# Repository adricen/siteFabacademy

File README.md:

adrien.centonze's website --> [See it online](http://fab.academany.org/2018/labs/fablabdigiscope/students/adrien-centonze/index.html)

# Multiple purpose machin

## Links:
* 3D files
( introduce a link from gitlab )

* Stocks Materials
  * 2 Delrin : 28€ / 500 mm² --> 12mm height
  * 1 DHCP : 26€ / 500 mm² --> 10mm height

* Electronics

###  Parametric 3D Model :
* [Process](#process)
  * [Inspiration](#inspi)
  * [Design Process](#design)
  * [Think about the stock](#stock)
  * [3D prototyping](#proto)
  * [Parametric design](#parametric)
* [Montage](#montage)
  * animated montage + video

###  Milling On the Shopbot OSB :
* [Preparation](#prepa)
  * [Create stock from reality](#stockCrea)
  * [Place elements](#places)
* [Setup](#setup)
  * [Stock](#stock)
  * [Orientation](#orientation)
  * [Zero point](#zero)
* [Tools](#tools)
  * [fablab speed and feeds calculators](#speedFeed)
  * [Setup your tools](#setTools)
* [Toolpaths](#toolpath)
  * [Parrallel 3D](#parrallele)
  * [Milling](#mill)
  * [2D Pocket](#pocket)
  * [2D contour](#contour)

### Machin Design

---

###  Design thinking :
####  Process
##### **Inspiration :**

To begin with this machin we choose to take two machin as reference. The first one is the one from Hector and the second one came from Nadya.   

#####  **Designing :**
The main goal we wanted to succed in making this machin so that anybody who have access to a milling machin could do this.

##### **Think about the stock and your machin :**
There is two main constrain that you couldn't avoid when doing a machin like that it's your stack, what size and weight is it.

##### milling prototyping
In order to know more about rack and minion, I made a first rack and minino with a junk of wood we had here in the lab.

Then I wanted to be sure of the joinery I made, so I made a simple milling test on our shopbot.

##### 3D prototyping
To be sure about the join I used I made some rapid prototyping with the milling machin first, and then with the 3D printer.

##### Parametric design
I know that I would have to make a lot of back and forth to succed to make this machin so I worked on making the joinery parametricaly depending on my stock height and my the smaller mill I have that could go that deep.

##### Montage
  ( animated montage + video )

###  Milling :
#### Preparation
##### Create stock from reality

Start by making a virtual reproducion of your stock. The Pom / Delerain we have make 500mmx501mm

##### Place elements
##### Setup
##### Stock
##### Orientation
##### Zero point
##### Tools
##### fablab speed and feeds calculators
##### Setup your tools
##### Toolpaths
##### Parrallel 3D
##### Milling
##### 2D Pocket
##### 2D contour

#### Mounting
* [Making the holes for ( les visses )](#holes)

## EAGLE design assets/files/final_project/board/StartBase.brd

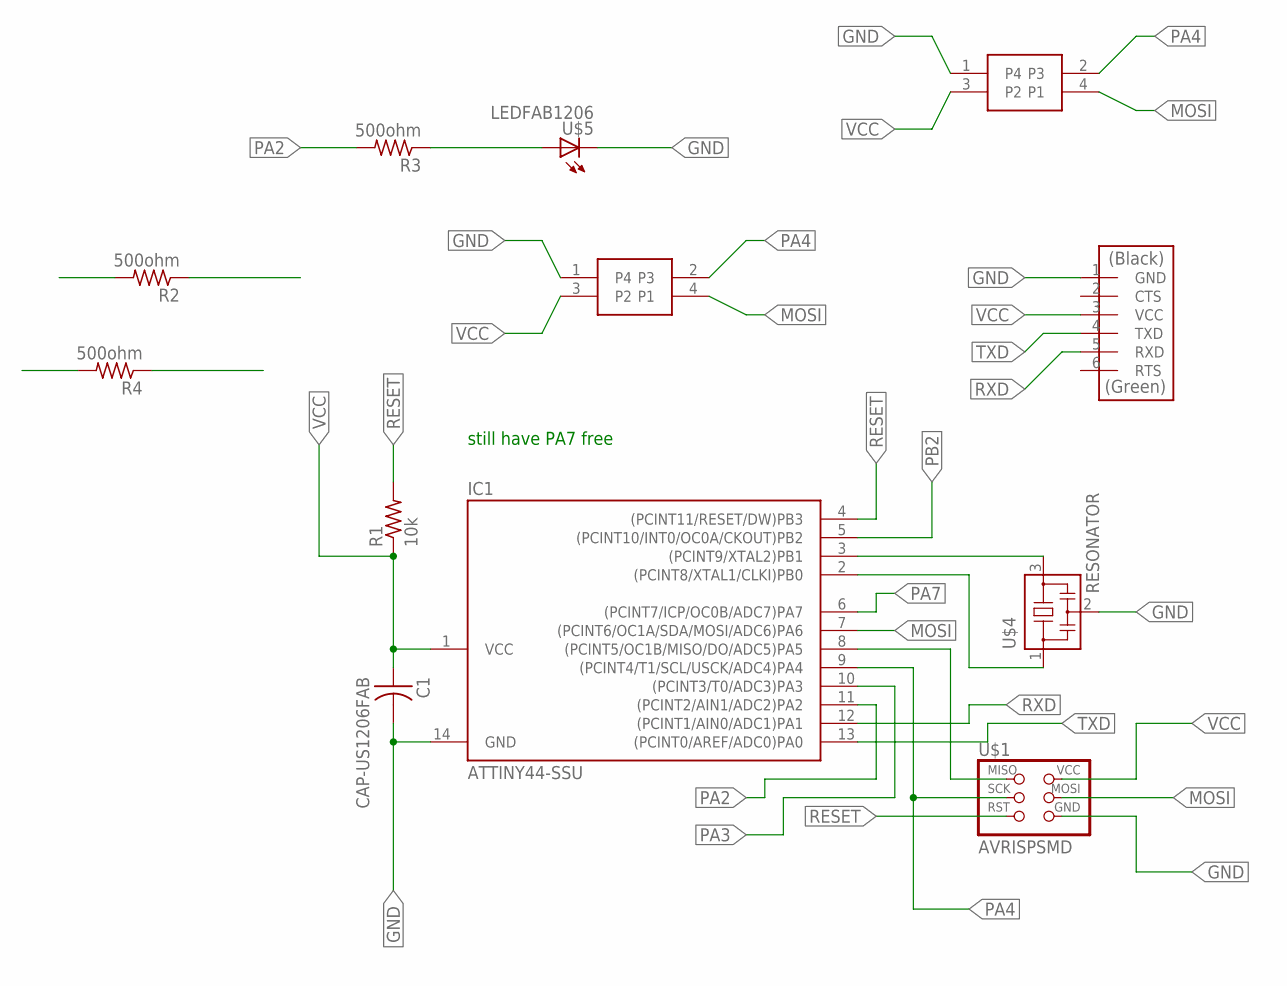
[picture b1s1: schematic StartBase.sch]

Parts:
C1: CAP-US1206FAB; C1206FAB
IC1: ATTINY44-SSU; SOIC14
R1: 10k; R1206FAB
R2, R3, R4: 500ohm; R1206FAB
U$1: AVRISPSMD; 2X03SMD
U$2: FTDI-SMD-HEADER; 1X06SMD
U$3, U$6: 4PIN-SMD-CONNECTOR; 2X02SMD
U$4: RESONATOR; EFOBM
U$5: LEDFAB1206; LED1206FAB

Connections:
GND: C1.2, IC1.14 (GND), U$1.6 (GND), U$2.1 (GND), U$3.1 (P4), U$4.2, U$5.2 (C), U$6.1 (P4)
MOSI: IC1.7 ((PCINT6/OC1A/SDA/MOSI/ADC6)PA6), U$1.4 (MOSI), U$3.4 (P1), U$6.4 (P1)
unnamed: IC1.3 ((PCINT9/XTAL2)PB1), U$4.3
unnamed: IC1.2 ((PCINT8/XTAL1/CLKI)PB0), U$4.1
unnamed: IC1.8 ((PCINT5/OC1B/MISO/DO/ADC5)PA5), U$1.1 (MISO)
unnamed: R3.1, U$5.1 (A)
PA1: R2.2
PA2: IC1.11 ((PCINT2/AIN1/ADC2)PA2), R3.2
PA3: IC1.10 ((PCINT3/T0/ADC3)PA3)
PA4: IC1.9 ((PCINT4/T1/SCL/USCK/ADC4)PA4), U$1.3 (SCK), U$3.2 (P3), U$6.2 (P3)
PA5: R4.2
PA7: IC1.6 ((PCINT7/ICP/OC0B/ADC7)PA7)
PB2: IC1.5 ((PCINT10/INT0/OC0A/CKOUT)PB2)
RESET: IC1.4 ((PCINT11/RESET/DW)PB3), R1.2, U$1.5 (RST)
RXD: IC1.12 ((PCINT1/AIN0/ADC1)PA1), U$2.5 (RXD)
TXD: IC1.13 ((PCINT0/AREF/ADC0)PA0), U$2.4 (TXD)
VCC: C1.1, IC1.1 (VCC), R1.1, U$1.2 (VCC), U$2.3 (VCC), U$3.3 (P2), U$6.3 (P2)

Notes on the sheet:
still have PA7 free

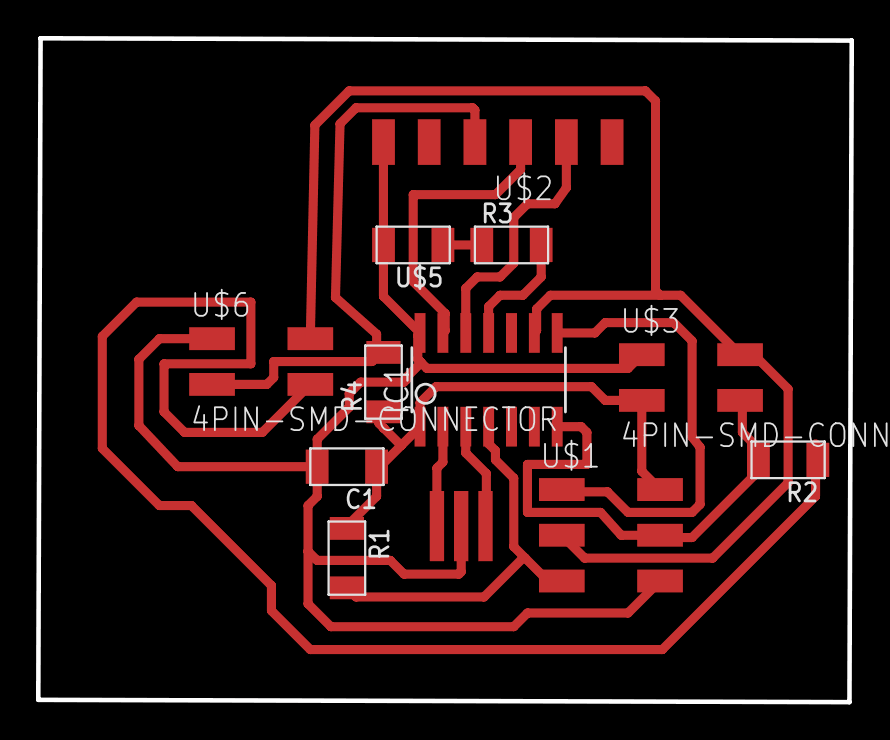
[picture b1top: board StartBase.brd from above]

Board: 2 copper layers, 45.2 x 36.9 mm, 12 parts (0 on the bottom side), 12 nets.

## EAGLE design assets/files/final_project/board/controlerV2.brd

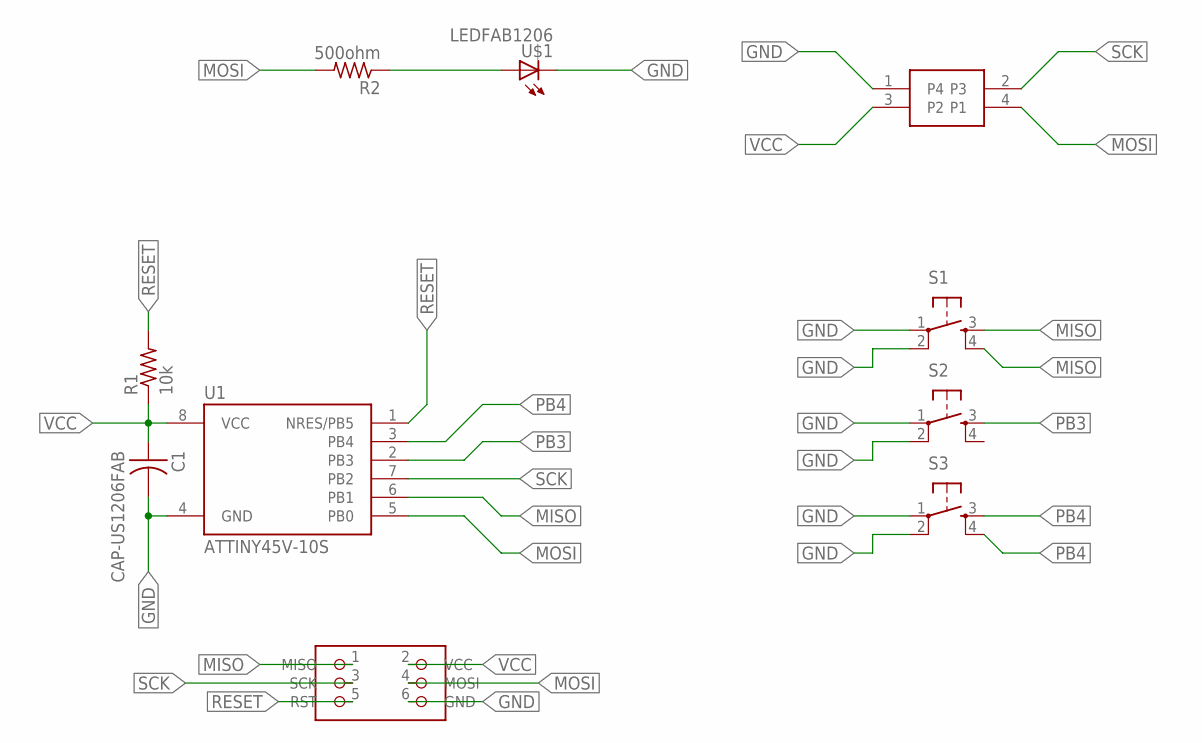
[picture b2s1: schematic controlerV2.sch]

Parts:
C1: CAP-US1206FAB; C1206FAB
R1: 10k; R1206
R2: 500ohm; R1206FAB
S1, S2, S3: 6MM_SWITCH6MM_SWITCH; 6MM_SWITCH
U1: ATTINY45V-10S; SOIC8_EIAJ_208MIL
U$1: LEDFAB1206; LED1206FAB
U$2: 4PIN-SMD-CONNECTOR; 2X02SMD
U$4: AVRISPSMD; 2X03SMD

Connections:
GND: C1.2, S1.1, S1.2 (P1), S2.1, S2.2 (P1), S3.1, S3.2 (P1), U1.4 (GND), U$1.2 (C), U$2.1 (P4), U$4.6 (GND)
MISO: S1.3 (S), S1.4 (S1), U1.6 (PB1), U$4.1 (MISO)
MOSI: R2.2, U1.5 (PB0), U$2.4 (P1), U$4.4 (MOSI)
unnamed: R2.1, U$1.1 (A)
PB3: S2.3 (S), U1.2 (PB3)
PB4: S3.3 (S), S3.4 (S1), U1.3 (PB4)
RESET: R1.2, U1.1 (NRES/PB5), U$4.5 (RST)
SCK: U1.7 (PB2), U$2.2 (P3), U$4.3 (SCK)
VCC: C1.1, R1.1, U1.8 (VCC), U$2.3 (P2), U$4.2 (VCC)

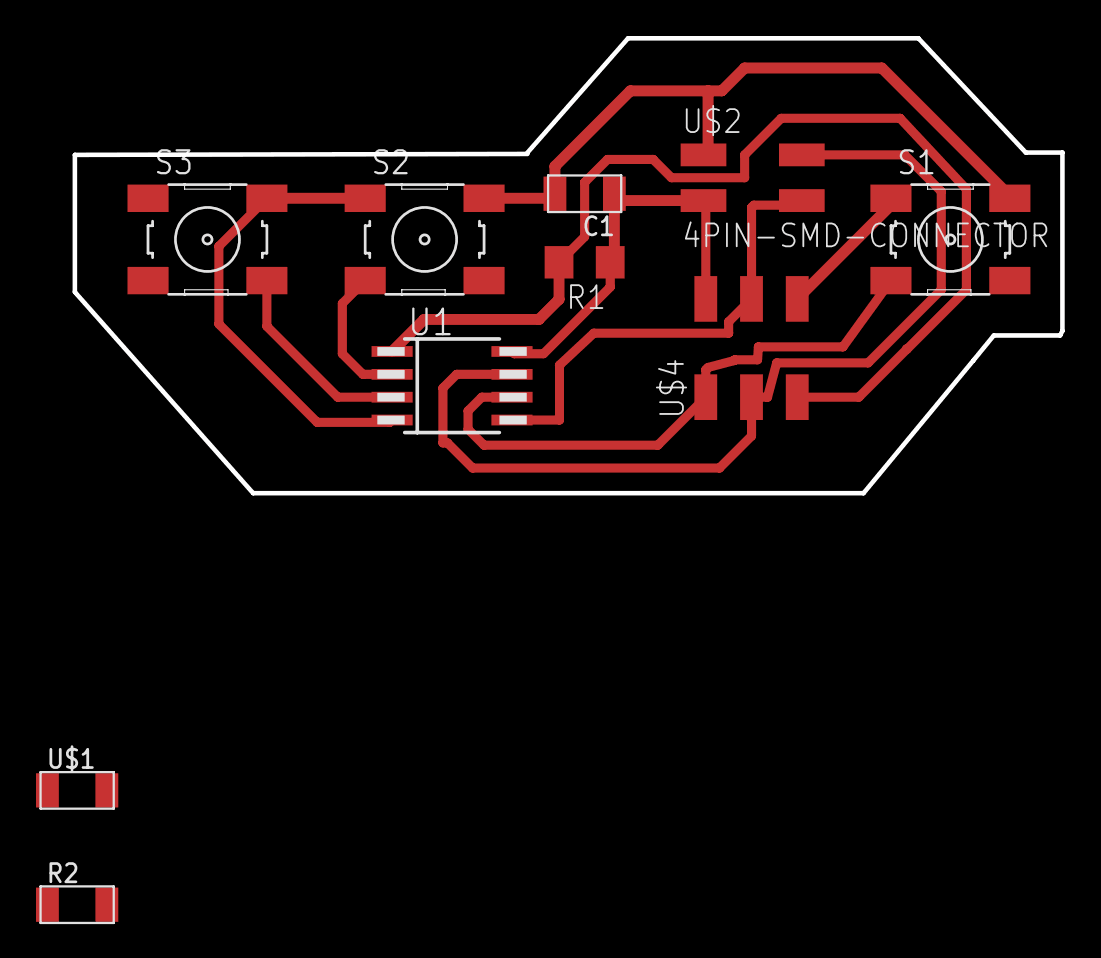
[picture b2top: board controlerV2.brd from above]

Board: 2 copper layers, 54.9 x 25.3 mm, 10 parts (0 on the bottom side), 9 nets.

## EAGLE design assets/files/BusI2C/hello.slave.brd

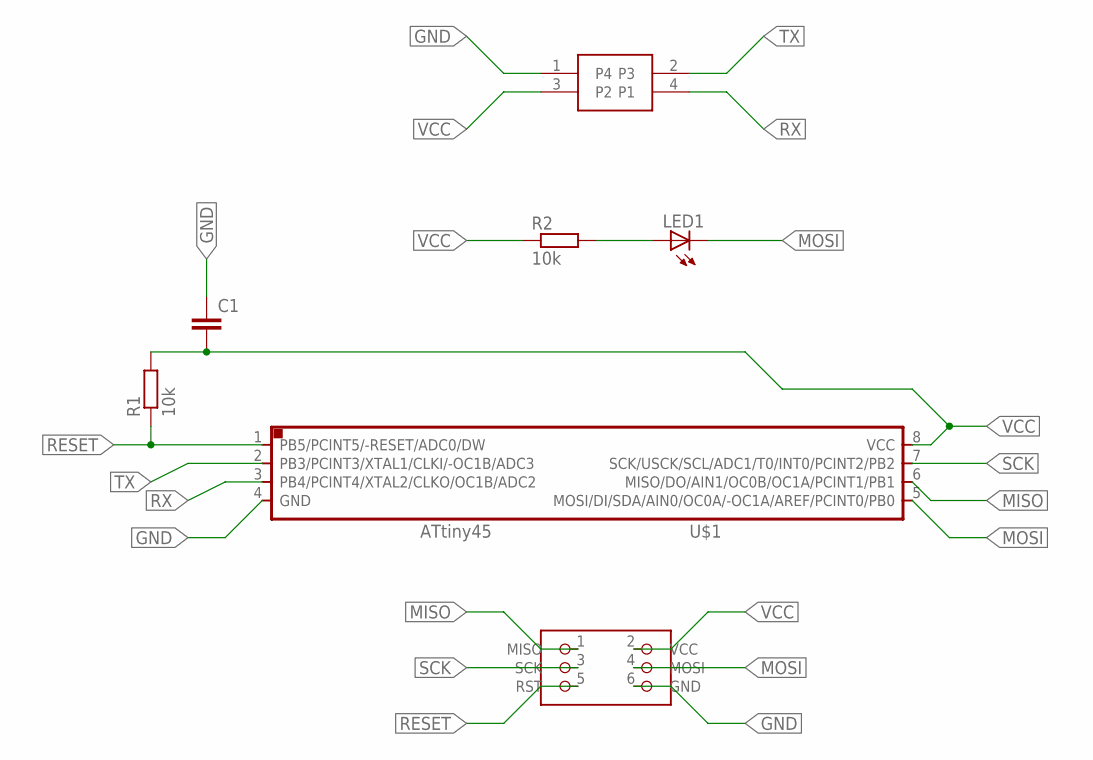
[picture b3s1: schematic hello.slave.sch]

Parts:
C1: C; C0805
LED1: LED_E; LED_1206
R1, R2: 10k; R0805
U$1: ATTINY45SI; SOIC8
U$2: AVRISPSMD; 2X03SMD
U$4: 4PIN-SMD-CONNECTOR; 2X02SMD

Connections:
GND: C1.1, U$1.4 (GND), U$2.6 (GND), U$4.1 (P4)
MISO: U$1.6 (MISO/DO/AIN1/OC0B/OC1A/PCINT1/PB1), U$2.1 (MISO)
MOSI: LED1.C, U$1.5 (MOSI/DI/SDA/AIN0/OC0A/-OC1A/AREF/PCINT0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), U$2.4 (MOSI)
unnamed: LED1.A, R2.2
RESET: R1.1, U$1.1 (PB5/PCINT5/-RESET/ADC0/DW), U$2.5 (RST)
RX: U$1.3 (PB4/PCINT4/XTAL2/CLKO/OC1B/ADC2), U$4.4 (P1)
SCK: U$1.7 (SCK/USCK/SCL/ADC1/T0/INT0/PCINT2/PB2), U$2.3 (SCK)
TX: U$1.2 (PB3/PCINT3/XTAL1/CLKI/-OC1B/ADC3), U$4.2 (P3)
VCC: C1.2, R1.2, R2.1, U$1.8 (VCC), U$2.2 (VCC), U$4.3 (P2)

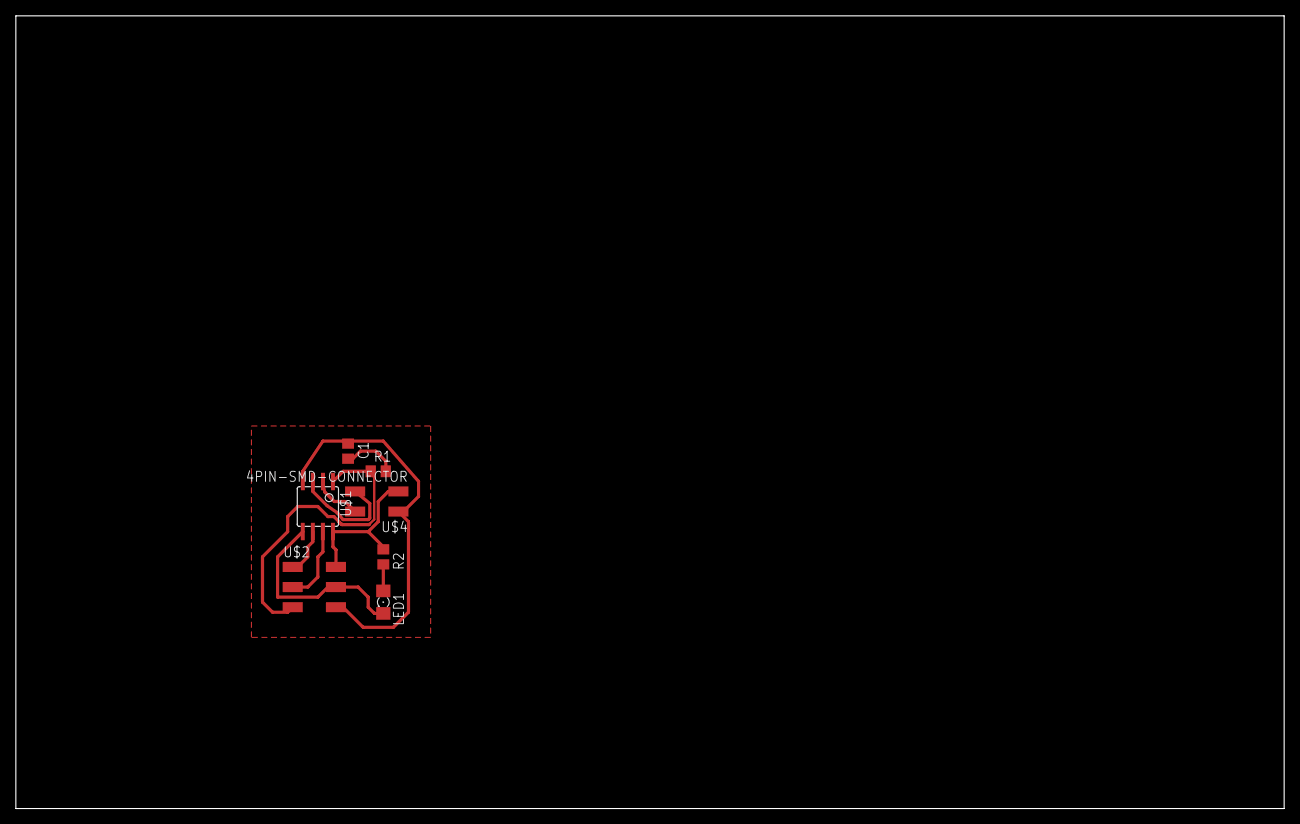
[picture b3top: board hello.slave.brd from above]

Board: 2 copper layers, 160.0 x 100.0 mm, 7 parts (0 on the bottom side), 9 nets.

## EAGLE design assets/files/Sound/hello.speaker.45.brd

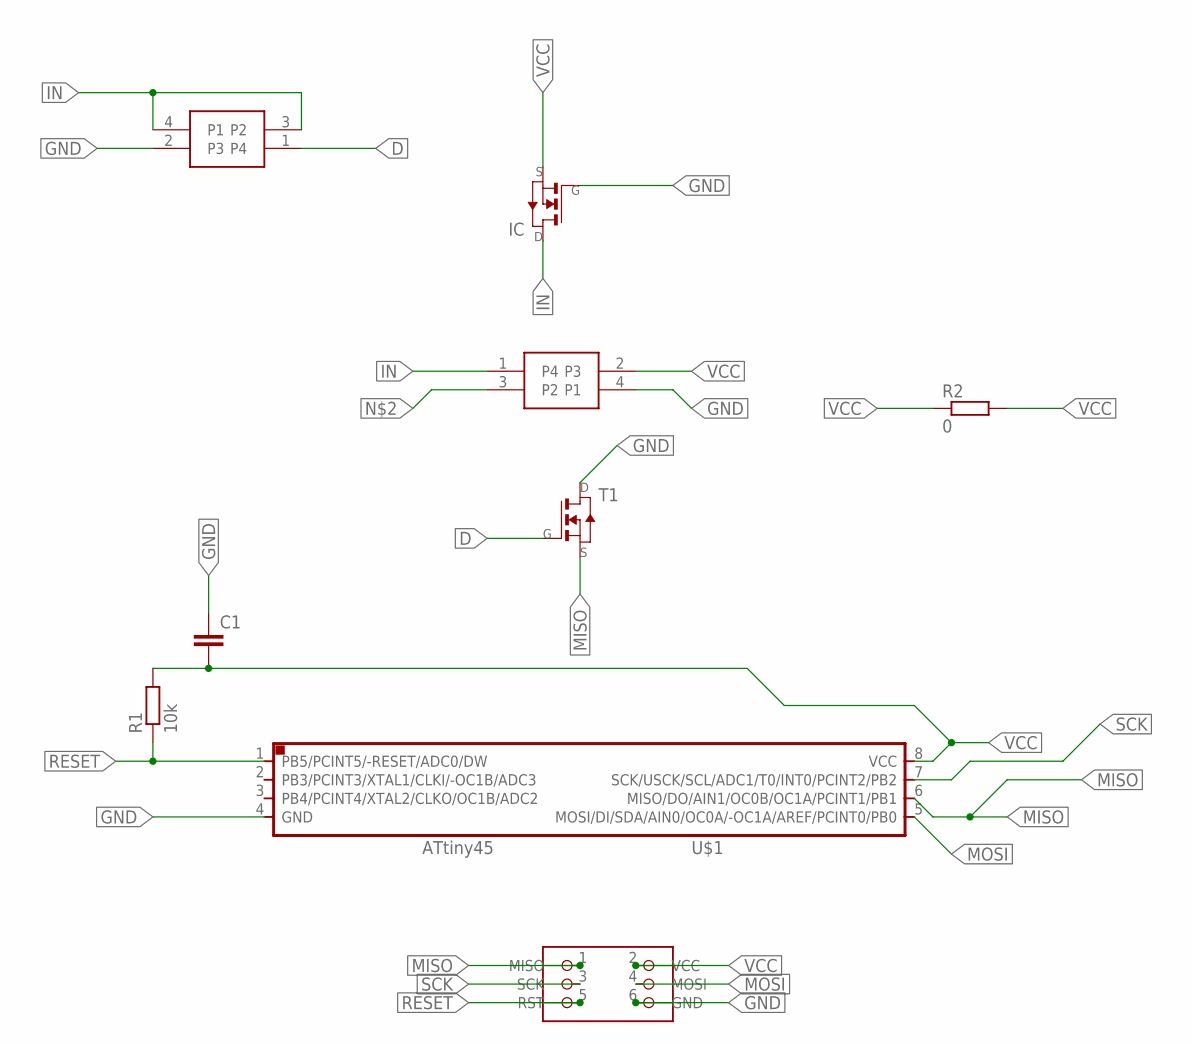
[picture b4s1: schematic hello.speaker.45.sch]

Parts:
C1: C; C0805
IC: NMOSFETSOT23; SOT-23
R1: 10k; R0805
R2: 0; R0805
T1: NMOSFETSOT23; SOT-23
U$1: ATTINY45SI; SOIC8
U$2: AVRISPSMD; 2X03SMD
U$3, U$4: 4PIN-SMD-CONNECTOR; 2X02SMD

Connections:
D: T1.3 (G), U$3.1 (P4)
GND: C1.1, IC.3 (G), T1.1 (D), U$1.4 (GND), U$2.6 (GND), U$3.2 (P3), U$4.4 (P1)
IN: IC.1 (D), U$3.3 (P2), U$3.4 (P1), U$4.1 (P4)
MISO: T1.2 (S), U$1.6 (MISO/DO/AIN1/OC0B/OC1A/PCINT1/PB1), U$2.1 (MISO)
MOSI: U$1.5 (MOSI/DI/SDA/AIN0/OC0A/-OC1A/AREF/PCINT0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), U$2.4 (MOSI)
RESET: R1.1, U$1.1 (PB5/PCINT5/-RESET/ADC0/DW), U$2.5 (RST)
SCK: U$1.7 (SCK/USCK/SCL/ADC1/T0/INT0/PCINT2/PB2), U$2.3 (SCK)
VCC: C1.2, IC.2 (S), R1.2, R2.1, R2.2, U$1.8 (VCC), U$2.2 (VCC), U$4.2 (P3)

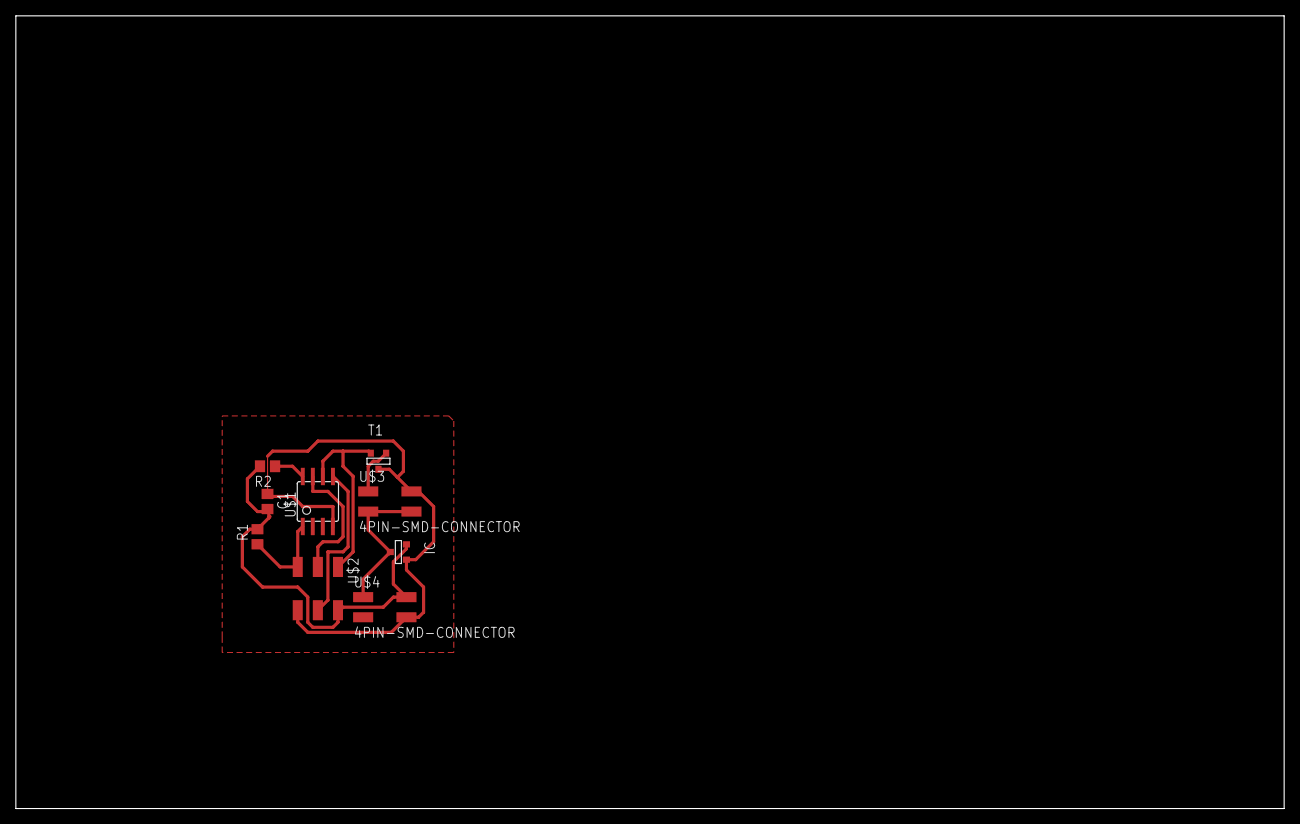
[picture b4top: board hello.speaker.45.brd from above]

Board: 2 copper layers, 160.0 x 100.0 mm, 9 parts (0 on the bottom side), 8 nets.

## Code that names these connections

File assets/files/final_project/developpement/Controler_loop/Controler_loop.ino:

/*
Controler PCB with ATtinny45
*/

//Pin names and function
//                              ISP   Inputs & Outputs
const byte S1 = 1; // pin6 PB1  MISO  S1
const byte S2 = 3; // pin2 PB3        S2
const byte S3 = 4; // pin3 PB4        S3
const byte SDA= 0; // pin5 PB0  MOSI  SDA
const byte SCL= 2; // pin7 PB2  SCK   SCL
//byte Test_pin = 5; // pin1-PB5-RESET Reserved for ISP Reset

//Variables
//                            
bool SW1=0; //Store read value of push button S1
bool SW2=0; //Store read value of push button S2
bool SW3=0; //Store read value of push button S3



void setup()
{
  pinMode(S1, INPUT);
  pinMode(S2, INPUT);
  pinMode(S3, INPUT);
  pinMode(SDA, OUTPUT);
  pinMode(SCL, OUTPUT);
  digitalWrite(SDA, LOW);
  digitalWrite(SCL, LOW);
}


void loop()
{
  //Read inputs
  
  SW1 = digitalRead(S1);
  SW2 = digitalRead(S2);
  SW3 = digitalRead(S3);


  //Send inputs reading over SDA/SCL
  
  digitalWrite(SCL, HIGH);
  digitalWrite(SDA, SW1);
  delay(1);   //8ms delay
  digitalWrite(SCL, LOW);
  digitalWrite(SDA, LOW);
  delay(1);

  digitalWrite(SCL, HIGH);
  digitalWrite(SDA, SW2);
  delay(1);
  digitalWrite(SCL, LOW);
  digitalWrite(SDA, LOW);
  delay(1);

  digitalWrite(SCL, HIGH);
  digitalWrite(SDA, SW3);
  delay(1);
  digitalWrite(SCL, LOW);
  digitalWrite(SDA, LOW);
  delay(1);

  delay(6); //6x8=48ms delay
      
}

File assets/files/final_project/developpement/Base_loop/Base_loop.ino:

/*
Base PCB with ATtinny44
*/

//Pin names and function
//                  
const byte RX = 0; // pin13 PA0 Tx Serial
const byte TX = 1; // pin12 PA1 Rx Serial

const byte SCL= 4; // pin9  PA4  SCL
const byte SDA= 6; // pin7  PA6  MOSI

const byte LED = 2; //pin11 PA2



//Variables
//
bool d=0; //store d-data and k-clock of custom com pipe
bool k=0;                          
bool SW1=0; //Store read value of push button S1
bool SW2=0; //Store read value of push button S2
bool SW3=0; //Store read value of push button S3
bool PSW1=0; //Store printed value of push button S1
bool PSW2=0; //Store printed value of push button S2
bool PSW3=0; //Store printed value of push button S3


#include <SoftwareSerial.h> //Tuto here: https://www.hackster.io/porrey/easy-serial-on-the-attiny-2676e6
//#define RX    0 // pin12 PA1 Rx Serial
//#define TX    1 // pin13 PA0 Tx Serial
SoftwareSerial Serial(RX, TX);



void setup()
{
  pinMode(SCL, INPUT);
  pinMode(SDA, INPUT);
  
  pinMode(LED, OUTPUT);
  digitalWrite(LED, LOW);

  digitalWrite(LED, HIGH);
  delay(1000); //1s delay
  digitalWrite(LED, LOW);
  delay(1000); //1s delay

  Serial.begin(9600);
  delay(10);
  Serial.println("Serial is awake at 9600");

  //Find beginning of transmission
  k=0;
  while(k==0){
    k=digitalRead(SCL);}
  delay(40);//data is sent at 2x48ms period
}


void loop()
{

  //Custom com Reading
  
  digitalWrite(LED, HIGH);

//  //Find beginning of transmission
//  k=0;
//  while(k==0){
//    k=digitalRead(SCL);}
//  digitalWrite(SDA, HIGH);
//  delay(40);//data is sent at 2x48ms period
//  digitalWrite(SDA, LOW);
//  digitalWrite(LED, LOW);
  
  k=0;
  while(k==0){
    k=digitalRead(SCL);}
  delay(1);
  SW1=digitalRead(SDA);
  delay(8);

  k=0;
  while(k==0){
    k=digitalRead(SCL);}
  delay(1);
  SW2=digitalRead(SDA);
  delay(8);

  k=0;
  while(k==0){
    k=digitalRead(SCL);}
  delay(1);
  SW3=digitalRead(SDA);
  delay(8);

  digitalWrite(LED, LOW);

  
  //Serial Print
  if ((PSW1!=SW1)|(PSW2!=SW2)|(PSW3!=SW3)) //print only if sth changed
  {
    // Serial.println(SW1);
    // Serial.println(SW2);
    // Serial.println(SW3);
    if(SW1 == 0){
      Serial.print("1");
    } 
    if(SW2 == 0){
      Serial.print("2");
      }
    if(SW3 == 0){
      Serial.print("3");
      }
      /*
    // Serial.print("SW1=");
    Serial.print(SW1,BIN);
    Serial.print(",");
    PSW1=SW1;
    // Serial.print("\tSW2=");
    Serial.print(SW2,BIN);
    Serial.print(",");
    PSW2=SW2;
    // Serial.print("\tSW3=");
    Serial.println(SW3  ,BIN);
    PSW3=SW3;
    */
  }
  //delay(10); //10ms delay

      
}

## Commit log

2018-01-22 Making the page public
2018-01-23 update du commit
2018-01-23 ajout des fichiers gitignore
2018-01-23 dding onez file
2018-01-23 reimport files avoiding error
2018-01-25 'refresh of the architecture'
2018-01-25 'test php'
2018-01-25 trying to make it work...
2018-01-25 update, maybe the probleme comme from bootstrap
2018-01-25 bootstrap en CDN
2018-01-25 remove stuffs
2018-01-25 mise en place du template php
2018-01-25 adding composer file
2018-01-25 test
2018-01-26 Upossiblefinal architecture
2018-01-26 html for new architecture
2018-01-27 major update
2018-01-27 ajustements largeur
2018-01-27 correction nav
2018-01-28 update documentation
2018-01-28 major update design
2018-01-28 Update file on phone
2018-01-28 Starting by writing
2018-01-29 mise a jour weeke 2
2018-01-29 update week2
2018-01-29 update week 2
2018-01-29 mise a jour du site
2018-01-30 Update week_1.md final project
2018-01-30 issue readme file
2018-01-30 ajout du fichier readme
2018-01-30 update margin
2018-02-01 arange architecture on documentation
2018-02-01 add url in readme
2018-02-01 arangement accueil avec liens directs
2018-02-01 test de merge
2018-02-02 update file size + demarage doc week3
2018-02-05 Update week_3.md - basic plan
2018-02-06 ajout update week3
2018-02-10 update parametric object
2018-02-10 up img
2018-02-10 uodate assignement week4
2018-02-10 up img size
2018-02-10 ajout file name
2018-02-10 correction img name
2018-02-11 update week4
2018-02-11 ajout de photos
2018-02-11 renam file
2018-02-13 push week 4
2018-02-14 enlevé edge
2018-02-14 ajout illu
2018-02-19 week 4 - engraved mire
2018-02-20 ajout week5
2018-02-24 update week5 to change computer
2018-02-24 changement img
2018-02-24 finalproj
2018-02-24 ajout accueil
2018-02-25 update doc
2018-02-25 update week6
2018-02-25 modif accueil
2018-02-27 ajout realisation Antimony
2018-02-27 ajout img
2018-02-27 correction img
2018-02-27 correction
2018-02-27 update doc ubuntu files
2018-02-27 adding a file folder
2018-02-27 minor correction
2018-02-27 ajout trucs
2018-02-27 resize img
2018-02-28 up scanning
2018-02-28 ajout antimony
2018-03-07 demarage semaine 7
2018-03-07 update pic
2018-03-07 retouche css
2018-03-09 train test done
2018-03-13 complements
2018-03-14 ajout des fichiers complements
2018-03-14 week 8 - big something
2018-03-20 ajout page week9
2018-03-21 ajout de la fin embed programming
2018-03-21 ajout de dig
2018-03-28 ajout electronic design
2018-04-07 after the break it gets on
2018-04-10 ajout de la week 10
2018-04-11 week11 started
2018-04-11 ajout final project and home page
2018-04-12 working on week11
2018-04-13 working on hellogame
2018-04-16 ajout image input devices
2018-04-17 finish week11 till final project and starting week12
2018-04-17 ajout des commade de base
2018-04-17 ajout demarage week12
2018-04-19 uh vers les deux repo
2018-04-23 update input ui
2018-04-23 working on makefile
2018-04-24 ajout image
2018-04-24 screen img
2018-04-24 ajout de contenus
2018-05-02 debut working on week14
2018-05-02 working on the good nav sidebar
2018-05-09 week15
2018-05-23 ajoutimage final project
2018-05-23 ajout nav
2018-06-05 retake 4 first pages
2018-06-09 ajout content
2018-06-10 correction final project
2018-06-10 ajout final project
2018-06-10 ajout final project in week 1
2018-06-10 pb image week4
2018-06-10 ajout des fichiers
2018-06-10 ajout warning week 4
2018-06-10 suppresse week0
2018-06-10 ajout derniere pages
2018-06-11 ajout de cnotenus
2018-06-11 ajout des derniere video
2018-06-12 ajout de fichiers
2018-06-14 ajout content final
2018-06-15 working on final project
2018-06-15 ajout stuff
2018-06-15 link correction final project
2018-06-15 final project controlers
2018-06-16 final project
2018-06-16 final project fusion360 milling
2018-06-18 ajout des slides
2018-06-20 adding properly compressed video
2018-06-20 students.md signature
2018-06-25 completing week13
2018-06-27 markdown correction
2018-06-27 screenshot I2C bus
2018-06-27 finished network communication
2018-06-29 ajout de truc urgents
2018-06-29 big Update Suppression des PNG to 10
2018-06-30 major update - Finished and polished week 17 and final project
2018-06-30 added some video in wild card and all interface programming text
2018-06-30 documentaion V0.1
2018-06-30 img size correction
2018-07-07 ajout video
2018-08-28 last changes 28/8
